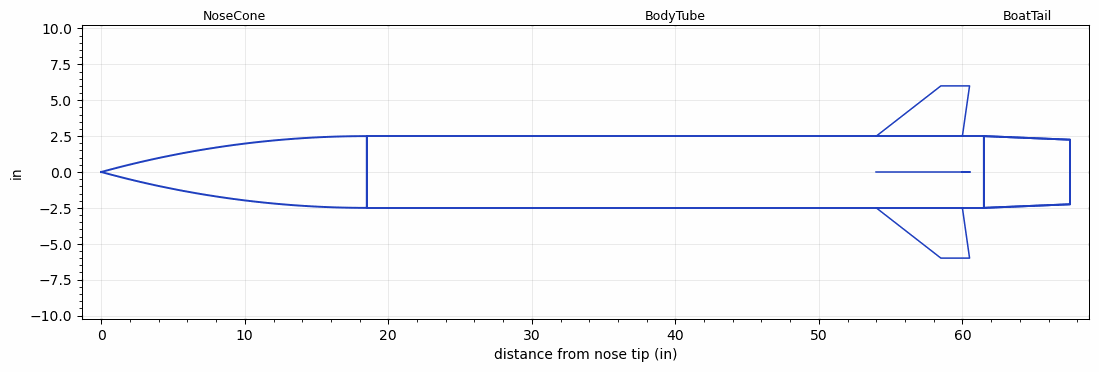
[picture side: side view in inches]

<RASAeroDocument>
 <FileVersion>2</FileVersion>
 <RocketDesign>
  <NoseCone>
   <Length>18.5</Length>
   <Diameter>5</Diameter>
   <Shape>Tangent Ogive</Shape>
   <Location>0</Location>
  </NoseCone>
  <BodyTube>
   <Length>43</Length>
   <Diameter>5</Diameter>
   <Location>18.5</Location>
   <BoattailLength>6</BoattailLength>
   <BoattailRearDiameter>4.5</BoattailRearDiameter>
   <Fin>
    <Count>4</Count>
    <Chord>6</Chord>
    <Span>3.5</Span>
    <SweepDistance>4.5</SweepDistance>
    <TipChord>2</TipChord>
    <Thickness>0.15</Thickness>
    <Location>7.5</Location>
    <AirfoilSection>Square</AirfoilSection>
   </Fin>
  </BodyTube>
  <BoatTail>
   <Length>6</Length>
   <Diameter>5</Diameter>
   <RearDiameter>4.5</RearDiameter>
   <Location>61.5</Location>
  </BoatTail>
  <Surface>Smooth (Zero Roughness)</Surface>
  <ModifiedBarrowman>False</ModifiedBarrowman>
  <Turbulence>True</Turbulence>
  <UseBooster1>False</UseBooster1>
  <UseBooster2>False</UseBooster2>
  <Comments>Reserved afterbody component study C-finned-boattail</Comments>
 </RocketDesign>
 <LaunchSite>
  <Altitude>0</Altitude>
  <Pressure>29.9214</Pressure>
  <RodAngle>0</RodAngle>
  <RodLength>6.5617</RodLength>
  <Temperature>59</Temperature>
  <WindSpeed>0</WindSpeed>
 </LaunchSite>
 <Recovery>
  <Altitude1>656.168</Altitude1>
  <Altitude2>0</Altitude2>
  <DeviceType1>Parachute</DeviceType1>
  <DeviceType2>None</DeviceType2>
  <Event1>True</Event1>
  <Event2>False</Event2>
  <Size1>24</Size1>
  <Size2>0</Size2>
  <EventType1>Apogee</EventType1>
  <EventType2>None</EventType2>
  <CD1>0.8</CD1>
  <CD2>0</CD2>
 </Recovery>
</RASAeroDocument>
